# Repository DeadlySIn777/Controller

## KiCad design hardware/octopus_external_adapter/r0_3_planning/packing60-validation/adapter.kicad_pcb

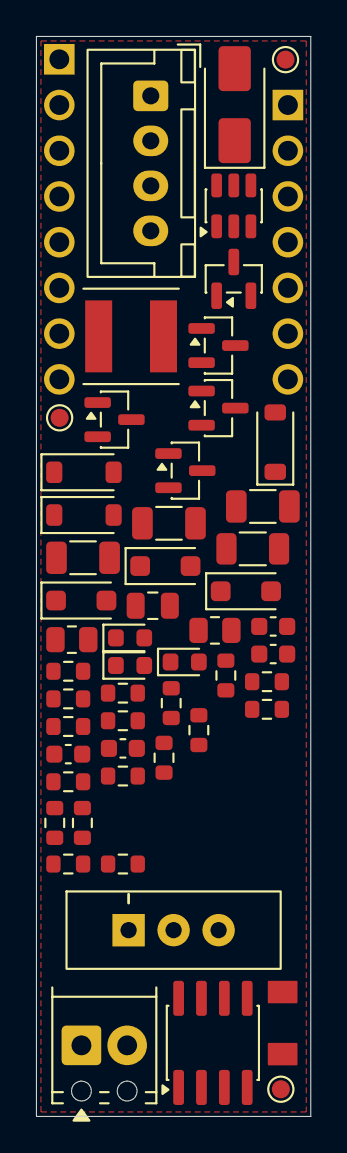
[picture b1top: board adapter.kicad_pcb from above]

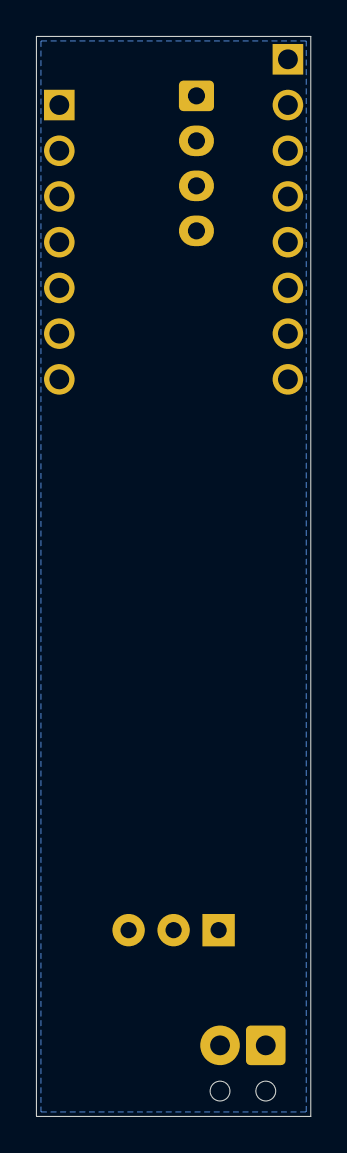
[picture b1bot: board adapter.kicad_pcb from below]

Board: 2 copper layers, 15.2 x 60.0 mm, 55 parts (2 on the bottom side), 33 nets, no tracks yet.

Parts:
C20, C25: 4.7uF 50V X7R 10%; C_1206_3216Metric
C21, C22: 100nF 50V X7R 10%; C_0603_1608Metric
C23: 22uF 25V X5R 10%; C_1206_3216Metric
C26: 2.2uF 25V X7R 10%; C_0805_2012Metric
C50, C51: 100nF 50V X7R; C_0603_1608Metric
D20: 28V bidirectional TVS; D_SMA
D21: 12V gate clamp; D_SOD-123
D22, D23, D25: 60V Schottky; D_SOD-123F
D24: 5.1V EN clamp; D_SOD-123
D26: 100V indicator input isolation; D_SOD-123
D50: 5V red LED; LED_0603_1608Metric
D51: 12V red LED; LED_0603_1608Metric
D52: 24V red LED; LED_0603_1608Metric
F20: 0.5A 63V fast fuse; Bourns_SF-1206F_3.1x1.55mm
J1: StepStick logic row; Wurth_61300811121_1x08_P2.54mm
J2: StepStick power row; VM physically omitted; Wurth_61300711121_1x07_P2.54mm
J3: Keyed driver signal output; JST_XH_B4B-XH-A_1x04_P2.50mm_Vertical
J4: External reference/power 5/12/24V; Phoenix_1725656_MPT_0p5_2_2p54_SilkClearance
L20: 15uH 20% Isat2.0A; L_Bourns_SRN5040
Q1, Q2, Q3: NX6008NBK; SOT-23
Q20: 60V reverse-polarity P-MOSFET; SOT-23
R1, R2, R3, R50, R51, R52: 1k 1%; R_0603_1608Metric
R4, R5, R6, R25: 10k 1%; R_0603_1608Metric
R20, R24: 100k 1%; R_0603_1608Metric
R21: 124k 0.1%; R_0603_1608Metric
R22: 23.7k 0.1%; R_0603_1608Metric
R23: 10k 1% 0.125W; R_0805_2012Metric
R26: 82ohm 1% 0.66W pulse-tolerant; R_1206_3216Metric
R27: 4.7k 1%; R_0603_1608Metric
R28: 330ohm 1% 0.125W; R_0805_2012Metric
R53: 100k 0.1% 25ppm/C; R_0603_1608Metric
R54: 3.9k 0.1% 25ppm/C; R_0603_1608Metric
SW1: 5V / EXT; E-Switch_EG1218_P040040
TP50: UPDI; TestPoint_Pad_D1.0mm
TP51: 3V3 SENSE ONLY; TestPoint_Pad_D1.0mm
TP52: GND; TestPoint_Pad_D1.0mm
U20: MP2459 adjustable buck ~5.06V; TSOT-23-6
U21: AP7375 3.3V indicator LDO; SOT-23
U50: ATtiny202 voltage indicator; SOIC-8_3.9x4.9mm_P1.27mm

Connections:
/BUCK_BST: C22.1, U20.1
/BUCK_EN: D24.1, R23.2, R24.1, U20.4
/BUCK_FB: R21.2, R22.1, U20.3
/BUCK_SW: C22.2, D23.1, L20.1, U20.6
/BUCK_VIN: C20.1, C21.1, D22.1, R23.1, U20.5
/COM_PLUS: J3.1, R25.1, R26.1, R53.1, SW1.2
/DIR: J1.8, R2.1
/DIR_GATE: Q2.1, R2.2, R5.1
/DIR_MINUS: J3.3, Q2.3
/EN: J1.1, R3.1
/ENA_MINUS: J3.4, Q3.3
/EN_GATE: Q3.1, R3.2, R6.1
/EXT_RAW: F20.1, J4.1
/GND: C20.2, C21.2, C23.2, C25.2, C26.2, C50.2, C51.2, D20.2, D23.2, D24.2, D50.1, D51.1, D52.1, J2.1, J2.7, J4.2, Q1.2, Q2.2, Q3.2, R4.2, R5.2, R6.2, R20.2, R22.2, R24.2, R25.2, R27.2, R28.2, R54.2, TP52.1, U20.2, U21.3, U50.8
/IND_ADC: C51.1, R53.2, R54.1, U50.4
/IND_FEED_R: D26.2, R26.2
/IND_LED5_A: D50.2, R50.2
/IND_LED12_A: D51.2, R51.2
/IND_LED24_A: D52.2, R52.2
/IND_LED_5V: R50.1, U50.2
/IND_LED_12V: R51.1, U50.3
/IND_LED_24V: R52.1, U50.5
/IND_UPDI: TP50.1, U50.6
/PUL_MINUS: J3.2, Q1.3
/REV_GATE: D21.2, Q20.1, R20.1
/STEP: J1.7, R1.1
/STEP_GATE: Q1.1, R1.2, R4.1
/V5_REG: C23.1, D25.2, L20.2, R21.1, R28.1
/V5_SELECT: D25.1, SW1.1
/V_EXT_FUSED: D20.1, F20.2, Q20.3
/V_EXT_PROT: D21.1, D22.2, Q20.2, SW1.3
/V_IND_3V3: C26.1, C50.1, R27.1, TP51.1, U21.2, U50.1
/V_IND_IN: C25.1, D26.1, U21.1
